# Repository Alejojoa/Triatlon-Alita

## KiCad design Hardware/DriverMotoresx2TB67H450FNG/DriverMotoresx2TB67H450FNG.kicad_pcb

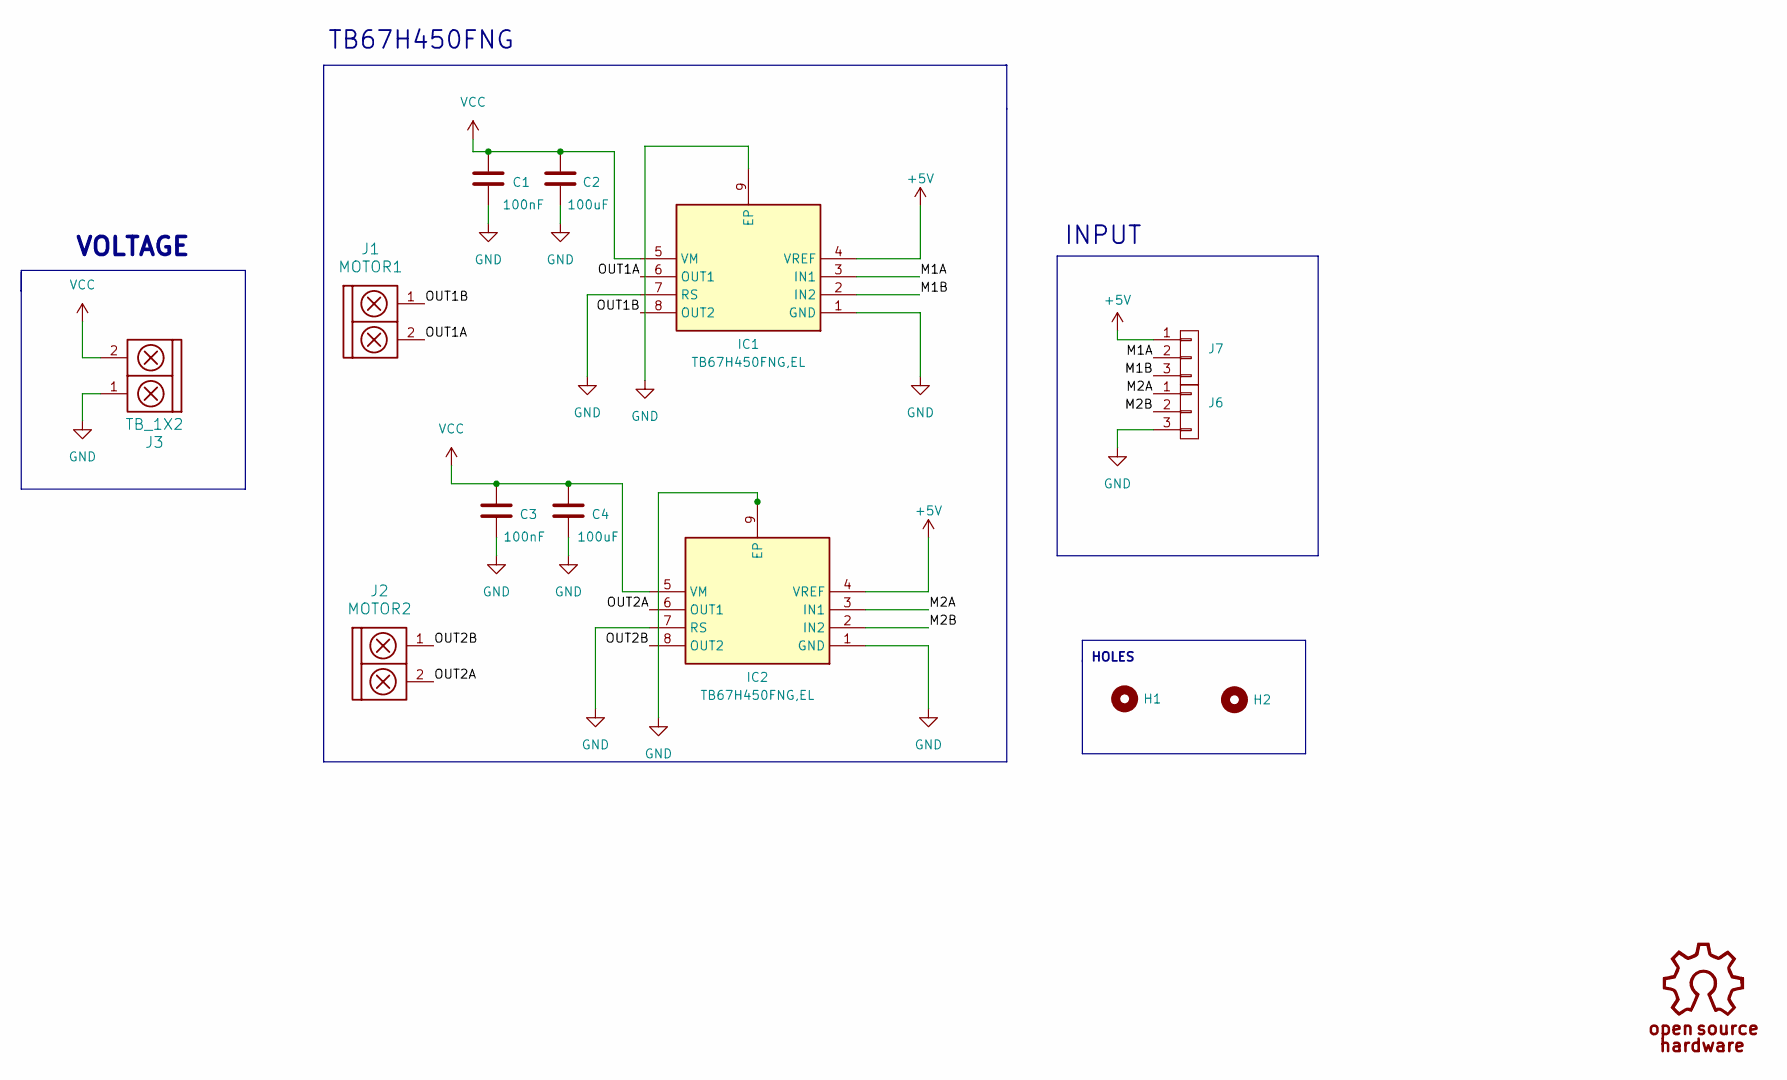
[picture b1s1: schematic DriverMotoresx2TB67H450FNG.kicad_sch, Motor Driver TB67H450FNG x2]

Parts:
C1, C3: 100nF; C_0805_2012Metric_Pad1.18x1.45mm_HandSolder
C2, C4: 100uF; CP_Radial_D10.0mm_P5.00mm
H1, H2: Mounting_Hole; hole_3mm
IC1, IC2: TB67H450FNG,EL; SOIC127P600X170-9N; Mouser Part Number 757-TB67H450FNGEL
J1: MOTOR1; BORNERA2_AZUL
J2: MOTOR2; BORNERA2_AZUL
J3: TB_1X2; BORNERA2_AZUL
J6, J7: Conn_01X03; PinHeader_1x03_P2.54mm_Vertical

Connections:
+5V: IC1.4 (VREF), IC2.4 (VREF), J7.1
/M1A: IC1.3 (IN1), J7.2
/M1B: IC1.2 (IN2), J7.3
/M2A: IC2.3 (IN1), J6.1
/M2B: IC2.2 (IN2), J6.2
/OUT1A: IC1.6 (OUT1), J1.2
/OUT1B: IC1.8 (OUT2), J1.1
/OUT2A: IC2.6 (OUT1), J2.2
/OUT2B: IC2.8 (OUT2), J2.1
GND: C1.2, C2.2, C3.2, C4.2, IC1.1 (GND), IC1.7 (RS), IC1.9 (EP), IC2.1 (GND), IC2.7 (RS), IC2.9 (EP), J3.1, J6.3
VCC: C1.1, C2.1, C3.1, C4.1, IC1.5 (VM), IC2.5 (VM), J3.2

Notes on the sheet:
HOLES
INPUT
TB67H450FNG
VOLTAGE

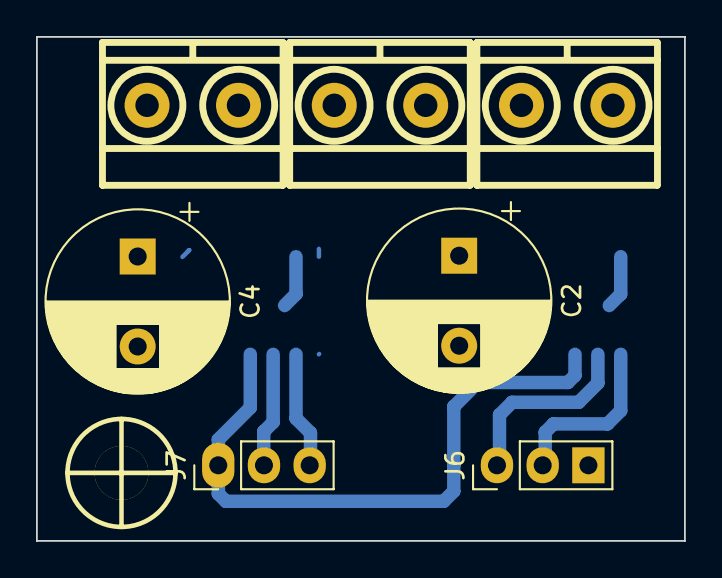
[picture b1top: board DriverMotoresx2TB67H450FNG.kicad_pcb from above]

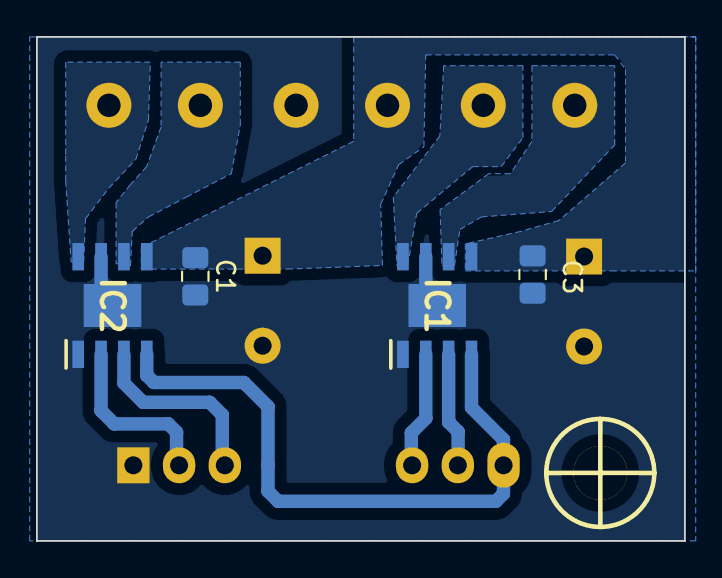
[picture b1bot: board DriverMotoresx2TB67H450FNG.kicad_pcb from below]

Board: 2 copper layers, 36.0 x 28.0 mm, 12 parts (4 on the bottom side), 11 nets.
